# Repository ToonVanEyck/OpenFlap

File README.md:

# OpenFlap

!!! warning

    🚨 This is still a work in progress. Using the the code and files in this repository to create your own display is not recommended at the moment! 🚨

The OpenFlap project aims to create a open source, affordable split-flap display for the makers and tinkerers of the world.
This repository houses all the required files to build, program and modify your very own split-flap display. 

[**Read the Docs**](https://toonvaneyck.github.io/OpenFlap/)

## Specifications

- 48 Flaps per module.
- 49mm x 70mm Character size.
- Stackable & Chainable.
- Daisy chain communication.
- Per module configuration & calibration.
- HTTP API available.
- Modular design.
- 3D printable parts.

## Design Philosophy

The OpenFlap system is designed to be modular and expandable, using common components and manufacturing techniques such as 3D printing and printed circuit boards.

The OpenFlap system uses DC geared motors instead of traditional stepper motors. This simplifies the mechanical design and reduces the cost of the system. Additionally this reduces the power consumption of the system and allows the split-flap display to rotate faster than the traditionally used stepper motors. 

The OpenFlap system is designed to be as plug and play as possible. The system is able to determine it's own display size, and should only require calibration once.

The OpenFlap system has a web interface that allows local control of the display. The web interface uses a HTTP API to communicate with the display, this API also allows external services to communicate with the display. No authentication or security measures are implemented at the moment.

The OpenFlap system can connect to your local WiFi network or host it's own network.

## I want to ...

[... know more about how the OpenFlap system works.](docs/architecture.md)

[... build my own OpenFlap display.](todo)

[... contribute to the OpenFlap project.](docs/developing.md)

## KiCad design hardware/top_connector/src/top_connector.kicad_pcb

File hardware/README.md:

Hardware
========

All PCB's are designed in Fusion 360, the source files can be accessed an copied through the links below:

Module
------
### Side Panel
- [side panel: Electronic Design](https://a360.co/3LnqHKp)
- [side panel: PCB](https://a360.co/3OHfgiH)
- [side panel: Schematic](https://a360.co/3EQSoZI)
- [side panel: 3D](https://a360.co/3vO3oD5)

### Flap
- [flap profile: PCB](https://a360.co/3KnExLN)
- [flap profile: 3D](https://a360.co/3KmTDAU)

### Encoder Wheel
- [wheel: PCB](https://a360.co/3LnqMxH)
- [wheel: 3D](https://a360.co/37JMbTs)

Top-Con
-------
- [top-con: Electronic Design](https://a360.co/3KmcPPo)
- [top-con: PCB](https://a360.co/36RFDl1)
- [top-con: Schematic](https://a360.co/3Mybp5H)
- [top-con: 3D](https://a360.co/3ETtb0O)

Controller
----------
- [controller: Electronic Design](https://a360.co/3vmdjzr)
- [controller: PCB](https://a360.co/3LnqmHD)
- [controller: Schematic](https://a360.co/3xTXOSp)
- [controller: 3D](https://a360.co/3rY5W0q)

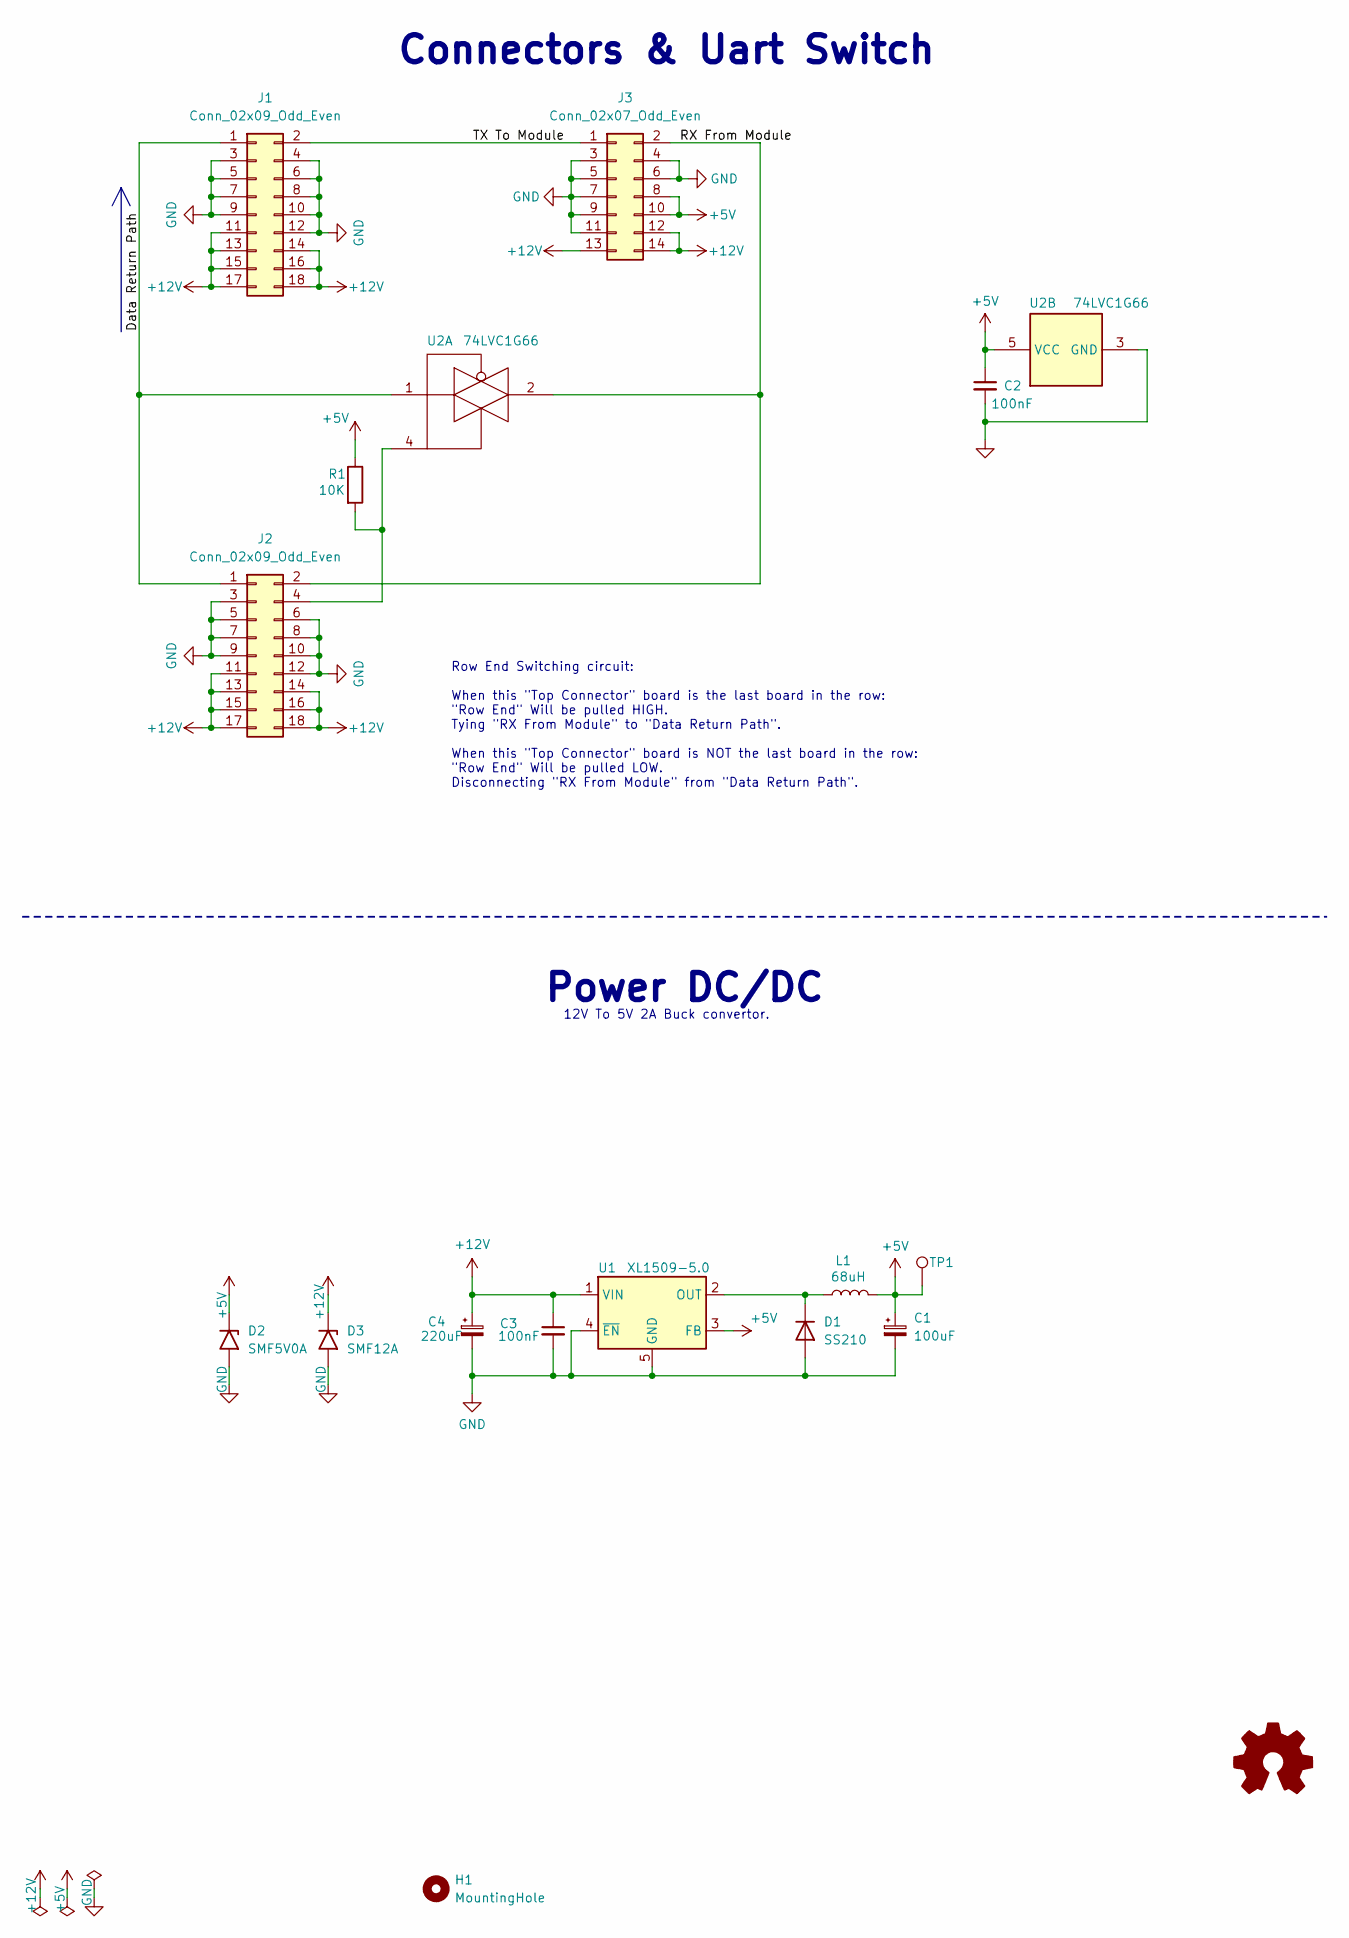
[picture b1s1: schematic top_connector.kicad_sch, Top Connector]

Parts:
C1: 100uF; CP_EIA-3528-21_Kemet-B; LCSC C16133
C2, C3: 100nF; C_0805_2012Metric
C4: 220uF; CP_Elec_6.3x7.7; LCSC C280399
D1: SS210; D_SMA; LCSC C14996
D2: SMF5V0A; D_SMF
D3: SMF12A; D_SMF
H1: MountingHole; MountingHole_2.7mm_M2.5
J1, J2: Conn_02x09_Odd_Even; IDC-Header_2x09_P2.54mm_Vertical
J3: Conn_02x07_Odd_Even; Samtec_HLE-107-02-xxx-DV-BE-A_2x07_P2.54mm_Horizontal
L1: 68uH; L_Sunlord_SWPA6045S; LCSC C53663
R1: 10K; R_0805_2012Metric
TP1: TestPoint; TestPoint_Pad_D1.5mm
U1: XL1509-5.0; SOIC-8_3.9x4.9mm_P1.27mm; LCSC C61063
U2: 74LVC1G66; SOT-23-5; LCSC C5375974

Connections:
+5V: C1.1, C2.1, D2.1 (A1), J3.8, J3.10, L1.2, R1.1, TP1.1, U1.3 (FB), U2.5 (VCC)
+12V: C3.1, C4.1, D3.1 (A1), J1.11, J1.13, J1.14, J1.15, J1.16, J1.17, J1.18, J2.11, J2.13, J2.14, J2.15, J2.16, J2.17, J2.18, J3.12, J3.13, J3.14, U1.1 (VIN)
/Data Return Path: J1.1, J2.1, U2.1
/RX From Module: J2.2, J3.2, U2.2
/TX To Module: J1.2, J3.1
GND: C1.2, C2.2, C3.2, C4.2, D1.2 (A), D2.2 (A2), D3.2 (A2), J1.3, J1.4, J1.5, J1.6, J1.7, J1.8, J1.9, J1.10, J1.12, J2.3, J2.5, J2.6, J2.7, J2.8, J2.9, J2.10, J2.12, J3.3, J3.4, J3.5, J3.6, J3.7, J3.9, J3.11, U1.4 (~EN), U1.5 (GND), U1.6 (GND), U1.7 (GND), U1.8 (GND), U2.3 (GND)
unnamed: D1.1 (K), L1.1, U1.2 (OUT)
unnamed: J2.4, R1.2, U2.4

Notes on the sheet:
Power DC/DC
12V To 5V 2A Buck convertor.
Row End Switching circuit: When this "Top Connector" board is the last board in the row: "Row End" Will be pulled HIGH. Tying "RX From Module" to "Data Return Path". When this "Top Connector" board is NOT the last board in the row: "Row End" Will be pulled LOW. Disconnecting "RX From Module" from "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
Connectors & Uart Switch

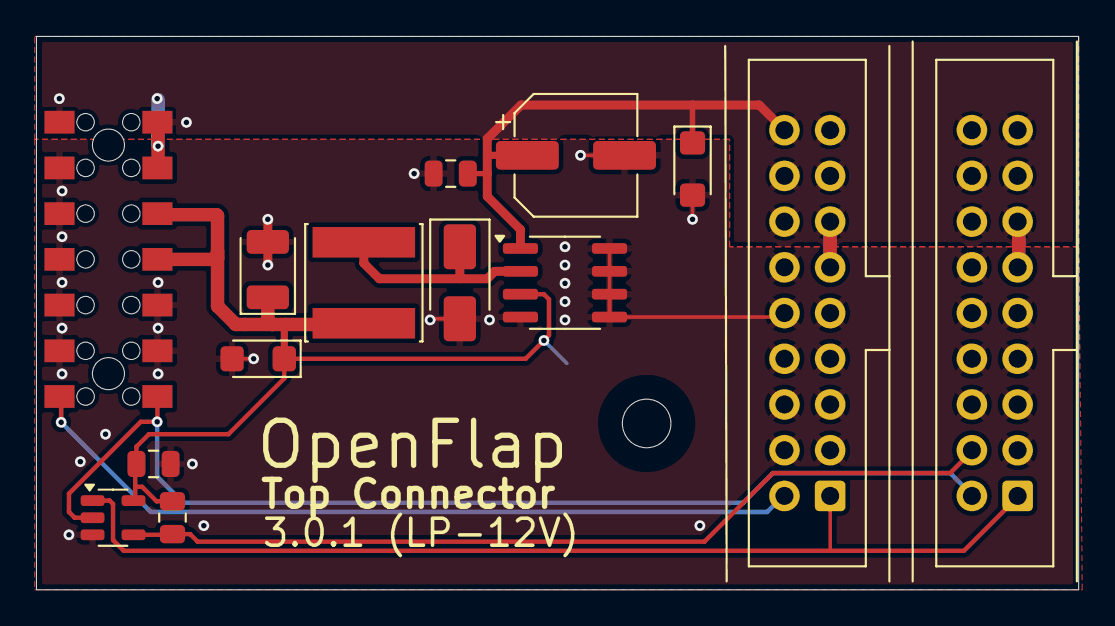
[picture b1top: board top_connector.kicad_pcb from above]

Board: 2 copper layers, 57.9 x 30.7 mm, 16 parts (1 on the bottom side), 8 nets.

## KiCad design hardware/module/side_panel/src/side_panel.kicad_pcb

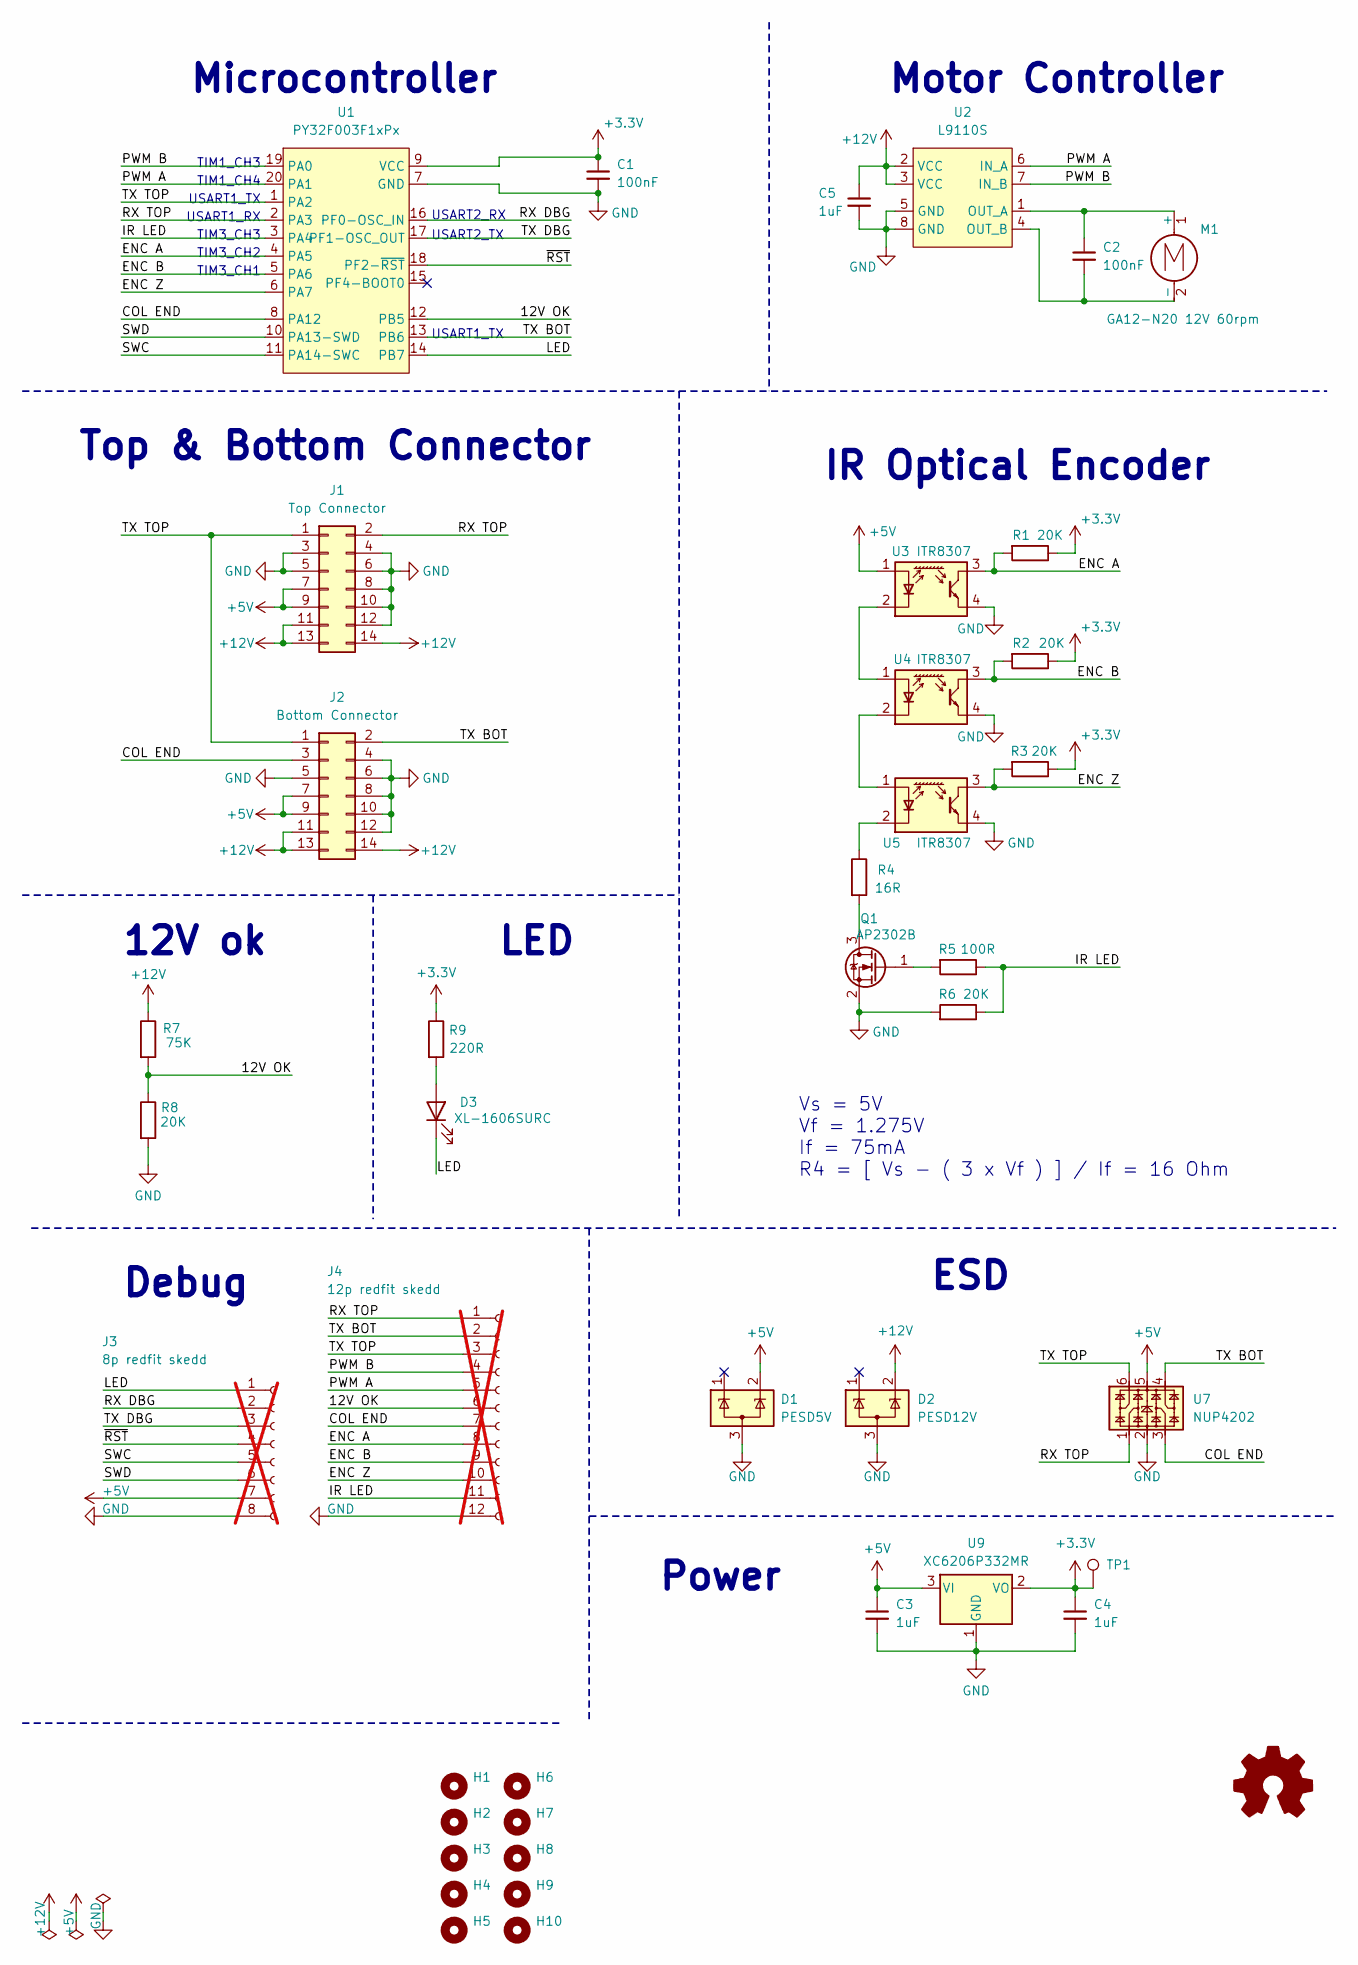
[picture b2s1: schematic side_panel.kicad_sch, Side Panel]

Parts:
C1, C2: 100nF; C_0805_2012Metric
C3, C4, C5: 1uF; C_0805_2012Metric
D1: PESD5V; SOT-23-3
D2: PESD12V; SOT-23-3
D3: XL-1606SURC; LED_Kingbright_APA1606_1.6x0.6mm_Horizontal; LCSC C965860
H1, H2, H3, H4, H5, H6, H7, H8, H9, H10: MountingHole; MountingHole_2.7mm
J1: Top Connector; PinHeader_2x07_P2.54mm_Horizontal
J2: Bottom Connector; PinSocket_2x07_P2.54mm_Horizontal
J3: 8p redfit skedd; 490107670812; not fitted
J4: 12p redfit skedd; 490107671212; not fitted
M1: GA12-N20 12V 60rpm; GA12-N20 Motor Vertical
Q1: AP2302B; SOT-23; LCSC C406812
R1, R2, R3, R6, R8: 20K; R_0805_2012Metric
R4: 16R; R_0805_2012Metric
R5: 100R; R_0805_2012Metric
R7: 75K; R_0805_2012Metric
R9: 220R; R_0805_2012Metric
TP1: TestPoint; TestPoint_Pad_D1.5mm
U1: PY32F003F1xPx; TSSOP-20_4.4x6.5mm_P0.65mm; LCSC C5379864
U2: L9110S; SOP-8_3.76x4.96mm_P1.27mm; LCSC C2984833
U3, U4, U5: ITR8307; OnSemi_CASE100CY; LCSC C81632
U7: NUP4202; SOT-23-6; LCSC C5199189
U9: XC6206P332MR; SOT-23-3

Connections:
+3.3V: C1.1, C4.1, R1.1, R2.1, R3.1, R9.1, TP1.1, U1.9 (VCC), U9.2 (VO)
+5V: C3.1, D1.2 (K), J1.7, J1.9, J2.7, J2.9, J3.7, U3.1 (A), U7.5, U9.3 (VI)
+12V: C5.1, D2.2 (K), J1.11, J1.13, J1.14, J2.11, J2.13, J2.14, R7.1, U2.2 (VCC), U2.3 (VCC)
/12V OK: J4.6, R7.2, R8.1, U1.12 (PB5)
/COL END: J2.3, J4.7, U1.8 (PA12), U7.3
/ENC A: J4.8, R1.2, U1.4 (PA5), U3.3
/ENC B: J4.9, R2.2, U1.5 (PA6), U4.3
/ENC Z: J4.10, R3.2, U1.6 (PA7), U5.3
/IR LED: J4.11, R5.1, R6.1, U1.3 (PA4)
/LED: D3.1 (K), J3.1, U1.14 (PB7)
/PWM A: J4.5, U1.20 (PA1), U2.6 (IN_A)
/PWM B: J4.4, U1.19 (PA0), U2.7 (IN_B)
/RX DBG: J3.2, U1.16 (PF0-OSC_IN)
/RX TOP: J1.2, J4.1, U1.2 (PA3), U7.1
/SWC: J3.5, U1.11 (PA14-SWC)
/SWD: J3.6, U1.10 (PA13-SWD)
/TX BOT: J2.2, J4.2, U1.13 (PB6), U7.4
/TX DBG: J3.3, U1.17 (PF1-OSC_OUT)
/TX TOP: J1.1, J2.1, J4.3, U1.1 (PA2), U7.6
/~RST: J3.4, U1.18 (PF2-~RST)
GND: C1.2, C3.2, C4.2, C5.2, D1.3 (A), D2.3 (A), J1.3, J1.4, J1.5, J1.6, J1.8, J1.10, J1.12, J2.4, J2.5, J2.6, J2.8, J2.10, J2.12, J3.8, J4.12, Q1.2 (S), R6.2, R8.2, U1.7 (GND), U2.5 (GND), U2.8 (GND), U3.4, U4.4, U5.4, U7.2, U9.1 (GND)
unnamed: D3.2 (A), R9.2
unnamed: C2.1, M1.1 (+), U2.1 (OUT_A)
unnamed: C2.2, M1.2 (-), U2.4 (OUT_B)
unnamed: Q1.3 (D), R4.2
unnamed: Q1.1 (G), R5.2
unnamed: U3.2 (K), U4.1 (A)
unnamed: U4.2 (K), U5.1 (A)
unnamed: R4.1, U5.2 (K)

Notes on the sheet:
USART1_RX
USART1_TX
LED
TIM1_CH3
Top & Bottom Connector
TIM3_CH2
Power
IR Optical Encoder
12V ok
TIM1_CH4
USART2_RX
TIM3_CH3
Vs = 5V Vf = 1.275V If = 75mA R4 = [ Vs - ( 3 x Vf ) ] / If = 16 Ohm
ESD
Motor Controller
Microcontroller
USART2_TX
TIM3_CH1
Debug

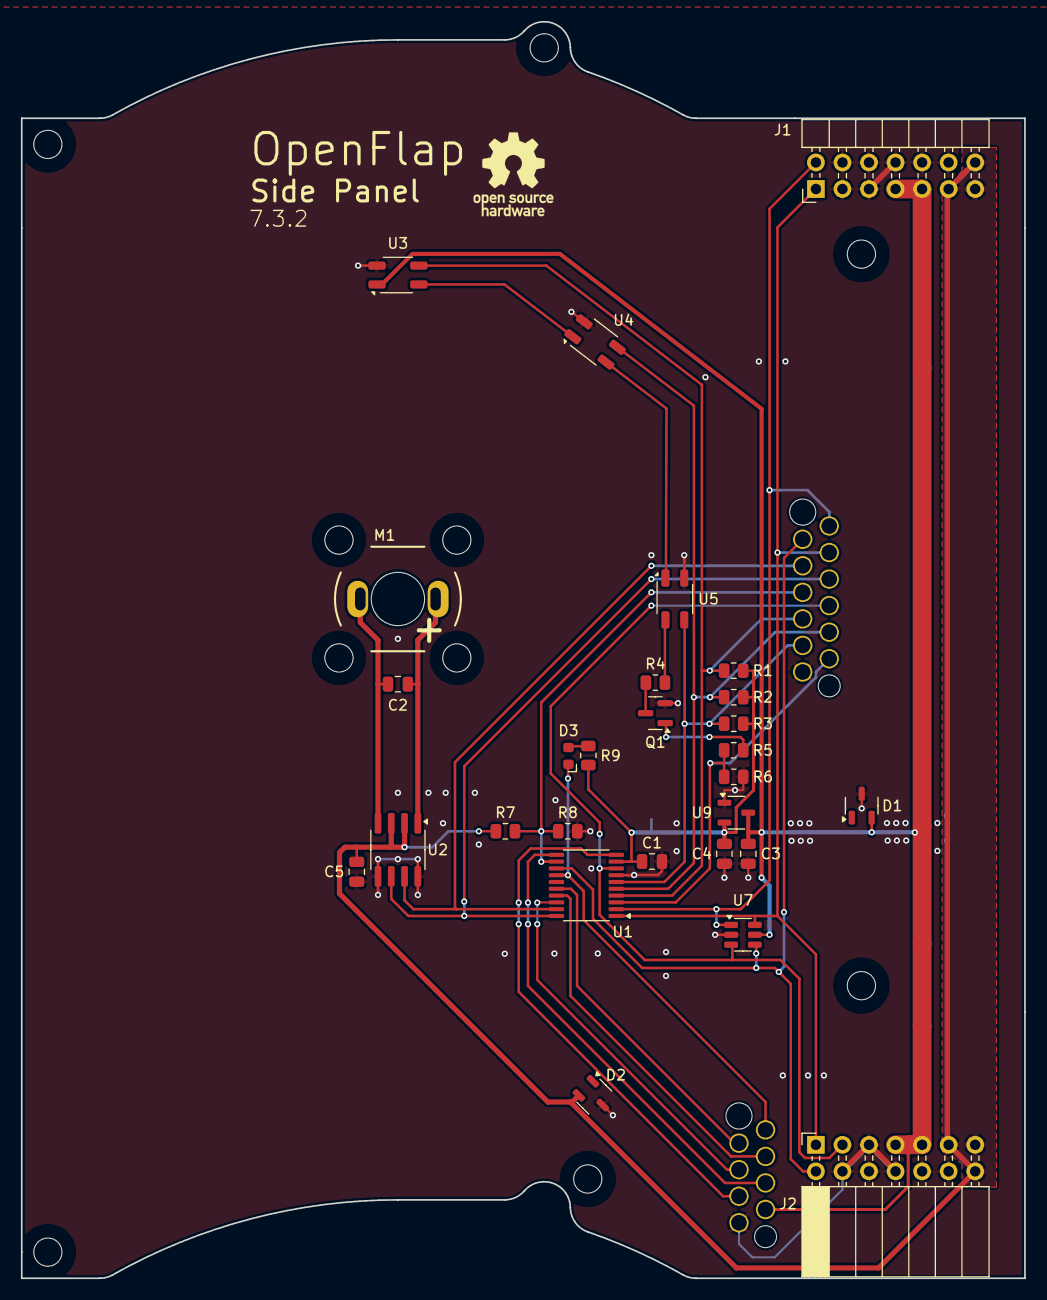
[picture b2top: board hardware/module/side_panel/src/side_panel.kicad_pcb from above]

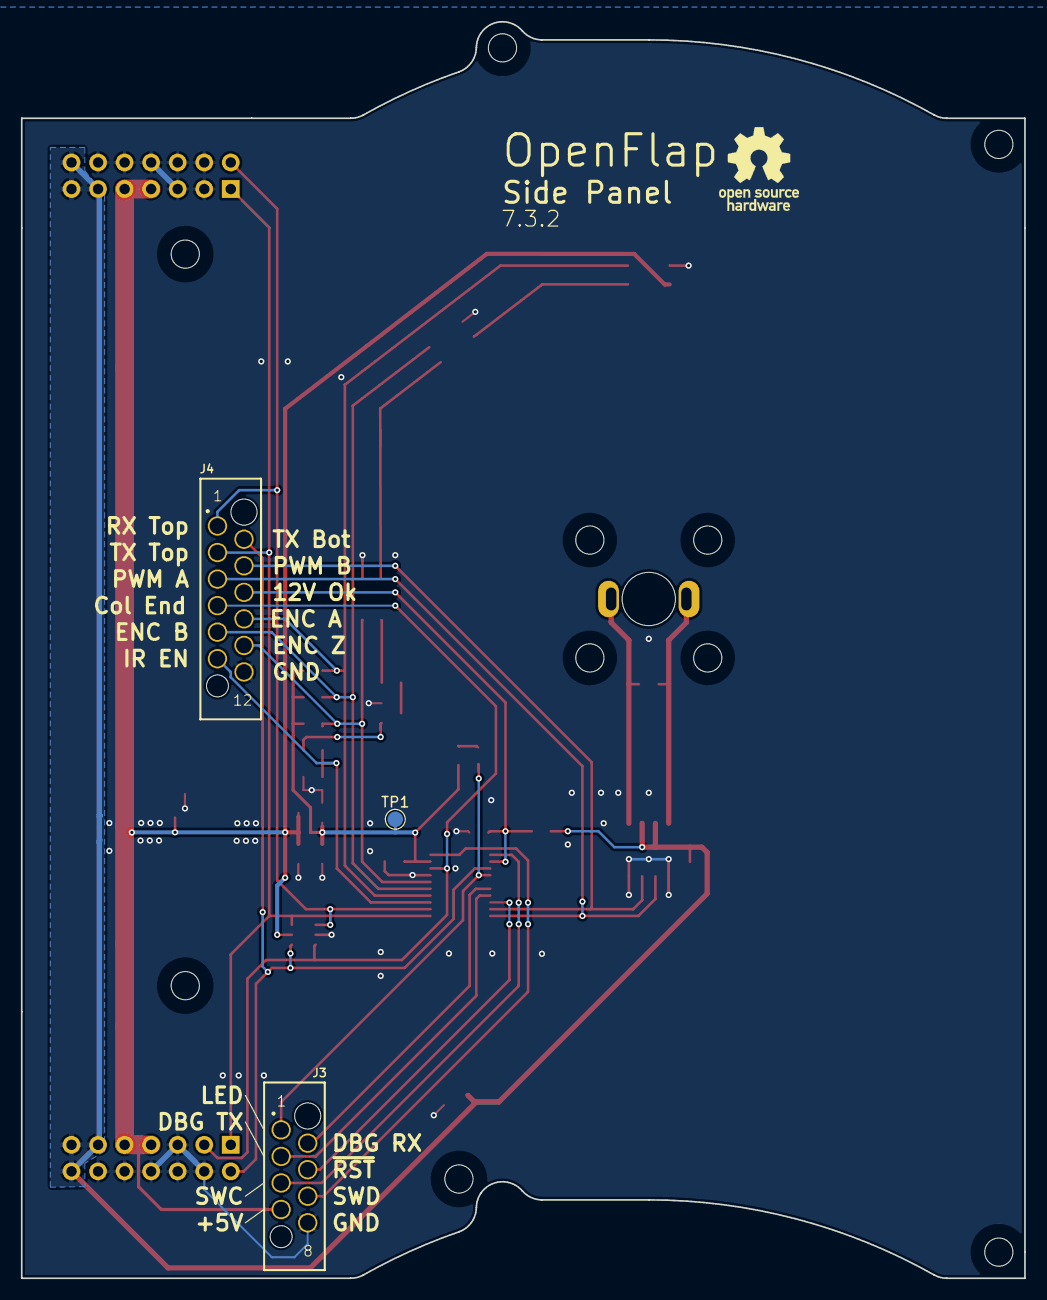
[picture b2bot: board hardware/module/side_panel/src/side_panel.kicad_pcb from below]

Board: 2 copper layers, 96.0 x 120.2 mm, 43 parts (4 on the bottom side), 29 nets.

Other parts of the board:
OSHW-LOGO-1, OSHW-LOGO-2: OSHW-Logo_7.5x8mm_SilkScreen

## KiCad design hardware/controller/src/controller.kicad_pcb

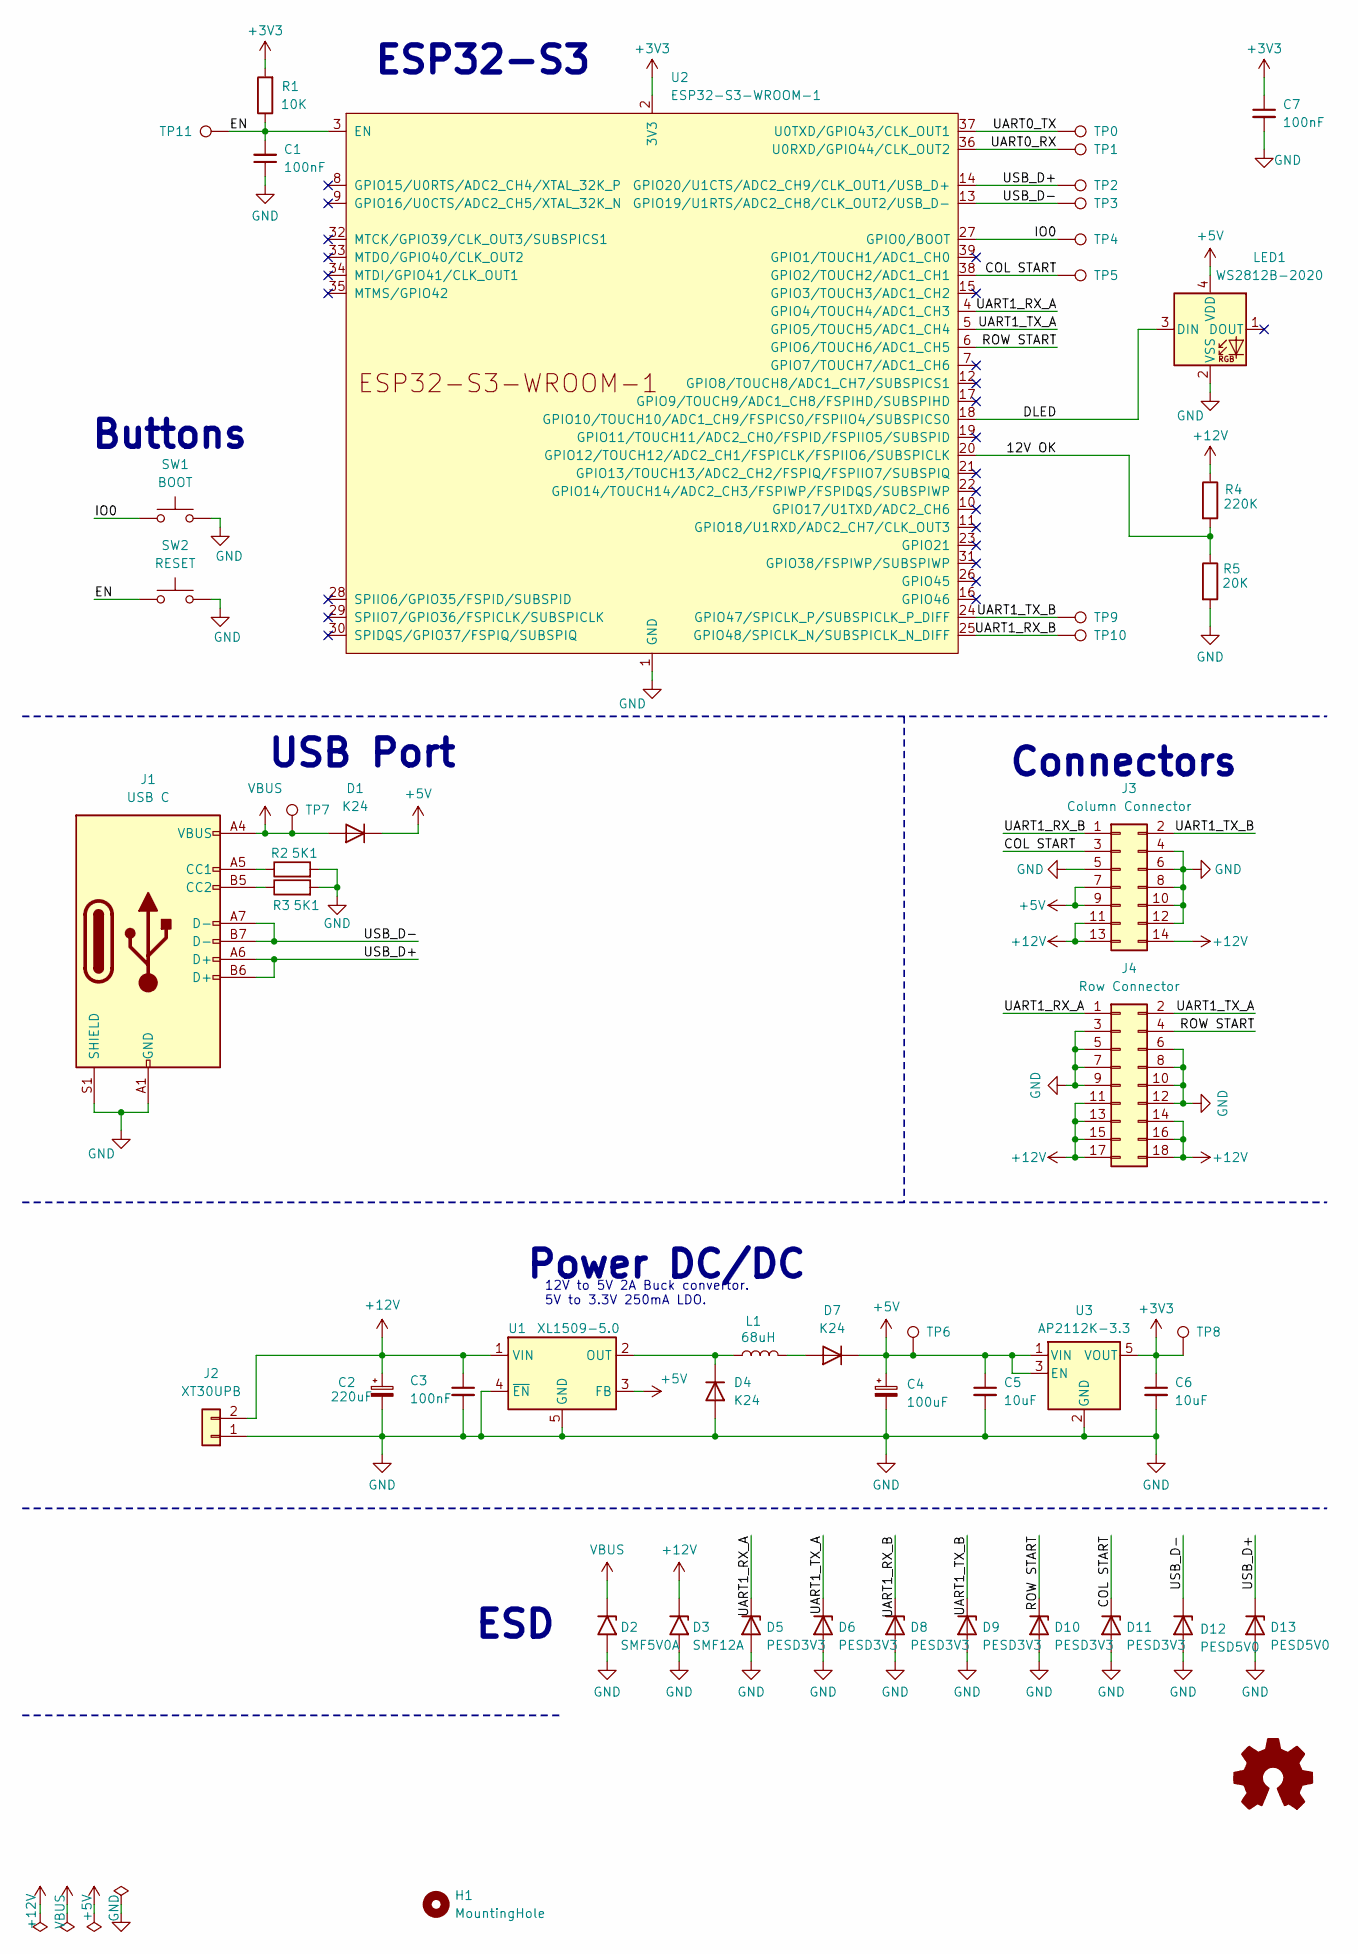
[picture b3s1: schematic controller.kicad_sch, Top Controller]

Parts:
C1, C3, C7: 100nF; C_0805_2012Metric
C2: 220uF; CP_Elec_6.3x7.7; LCSC C280399
C4: 100uF; CP_EIA-3528-21_Kemet-B; LCSC C16133
C5, C6: 10uF; C_0805_2012Metric
D1, D4, D7: K24; D_SMF; LCSC C5199107
D2: SMF5V0A; D_SMF
D3: SMF12A; D_SMF
D5, D6, D8, D9, D10, D11: PESD3V3; D_SOD-523; LCSC C5180303
D12, D13: PESD5V0; D_SOD-523; LCSC C19725076
H1: MountingHole; MountingHole_2.7mm_M2.5
J1: USB C; MC-803LS-HXXX; LCSC C3039302
J2: XT30UPB; AMASS_XT30UPB-M_1x02_P5.0mm_Vertical; LCSC C428721
J3: Column Connector; Samtec_HLE-107-02-xxx-DV-BE-A_2x07_P2.54mm_Horizontal
J4: Row Connector; IDC-Header_2x09_P2.54mm_Vertical
L1: 68uH; L_Sunlord_SWPA6045S; LCSC C53663
LED1: WS2812B-2020; LED_WS2812B-2020_PLCC4_2.0x2.0mm; LCSC C41413181
R1: 10K; R_0603_1608Metric
R2, R3: 5K1; R_0603_1608Metric
R4: 220K; R_0603_1608Metric
R5: 20K; R_0603_1608Metric
SW1: BOOT; SW_SPST_EVQP7C; LCSC C528965
SW2: RESET; SW_SPST_EVQP7C; LCSC C528965
TP0, TP1, TP2, TP3, TP4, TP5, TP6, TP7, TP8, TP9, TP10, TP11: TestPoint; TestPoint_Pad_D1.5mm
U1: XL1509-5.0; SOIC-8_3.9x4.9mm_P1.27mm; LCSC C61063
U2: ESP32-S3-WROOM-1
U3: AP2112K-3.3; SOT-23-5

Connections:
+3V3: C6.1, C7.1, R1.2, TP8.1, U2.2 (3V3), U3.5 (VOUT)
+5V: C4.1, C5.1, D1.1 (K), D7.1 (K), J3.7, J3.9, LED1.4 (VDD), TP6.1, U1.3 (FB), U3.1 (VIN), U3.3 (EN)
+12V: C2.1, C3.1, D3.1 (A1), J2.2, J3.11, J3.13, J3.14, J4.11, J4.13, J4.14, J4.15, J4.16, J4.17, J4.18, R4.1, U1.1 (VIN)
/12V OK: R4.2, R5.1, U2.20 (GPIO12/TOUCH12/ADC2_CH1/FSPICLK/FSPIIO6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)
/COL START: D11.1 (K), J3.3, TP5.1, U2.38 (GPIO2/TOUCH2/ADC1_CH1)
/DLED: LED1.3 (DIN), U2.18 (GPIO10/TOUCH10/ADC1_CH9/FSPICS0/FSPIIO4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)
/EN: C1.2, R1.1, SW2.1, TP11.1, U2.3 (EN)
/IO0: SW1.1, TP4.1, U2.27 (GPIO0/BOOT)
/ROW START: D10.1 (K), J4.4, U2.6 (GPIO6/TOUCH6/ADC1_CH5)
/UART0_RX: TP1.1, U2.36 (U0RXD/GPIO44/CLK_OUT2)
/UART0_TX: TP0.1, U2.37 (U0TXD/GPIO43/CLK_OUT1)
/UART1_RX_A: D5.1 (K), J4.1, U2.4 (GPIO4/TOUCH4/ADC1_CH3)
/UART1_RX_B: D8.1 (K), J3.1, TP10.1, U2.25 (GPIO48/SPICLK_N/SUBSPICLK_N_DIFF)
/UART1_TX_A: D6.1 (K), J4.2, U2.5 (GPIO5/TOUCH5/ADC1_CH4)
/UART1_TX_B: D9.1 (K), J3.2, TP9.1, U2.24 (GPIO47/SPICLK_P/SUBSPICLK_P_DIFF)
/USB_D+: D13.1 (K), J1.A6 (D+), J1.B6 (D+), TP2.1, U2.14 (GPIO20/U1CTS/ADC2_CH9/CLK_OUT1/USB_D+)
/USB_D-: D12.1 (K), J1.A7 (D-), J1.B7 (D-), TP3.1, U2.13 (GPIO19/U1RTS/ADC2_CH8/CLK_OUT2/USB_D-)
GND: C1.1, C2.2, C3.2, C4.2, C5.2, C6.2, C7.2, D2.2 (A2), D3.2 (A2), D4.2 (A), D5.2 (A), D6.2 (A), D8.2 (A), D9.2 (A), D10.2 (A), D11.2 (A), D12.2 (A), D13.2 (A), J1.A1 (GND), J1.A12 (GND), J1.B1 (GND), J1.B12 (GND), J1.S1 (SHIELD), J2.1, J3.4, J3.5, J3.6, J3.8, J3.10, J3.12, J4.3, J4.5, J4.6, J4.7, J4.8, J4.9, J4.10, J4.12, LED1.2 (VSS), R2.2, R3.2, R5.2, SW1.2, SW2.2, U1.4 (~EN), U1.5 (GND), U1.6 (GND), U1.7 (GND), U1.8 (GND), U2.1 (GND), U2.40 (GND), U2.41 (GND), U3.2 (GND)
unnamed: D4.1 (K), L1.1, U1.2 (OUT)
unnamed: D7.2 (A), L1.2
unnamed: J1.A5 (CC1), R2.1
unnamed: J1.B5 (CC2), R3.1
VBUS: D1.2 (A), D2.1 (A1), J1.A4 (VBUS), J1.A9 (VBUS), J1.B4 (VBUS), J1.B9 (VBUS), TP7.1

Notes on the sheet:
Power DC/DC
ESD
Buttons
USB Port
12V to 5V 2A Buck convertor. 5V to 3.3V 250mA LDO.
Connectors
ESP32-S3

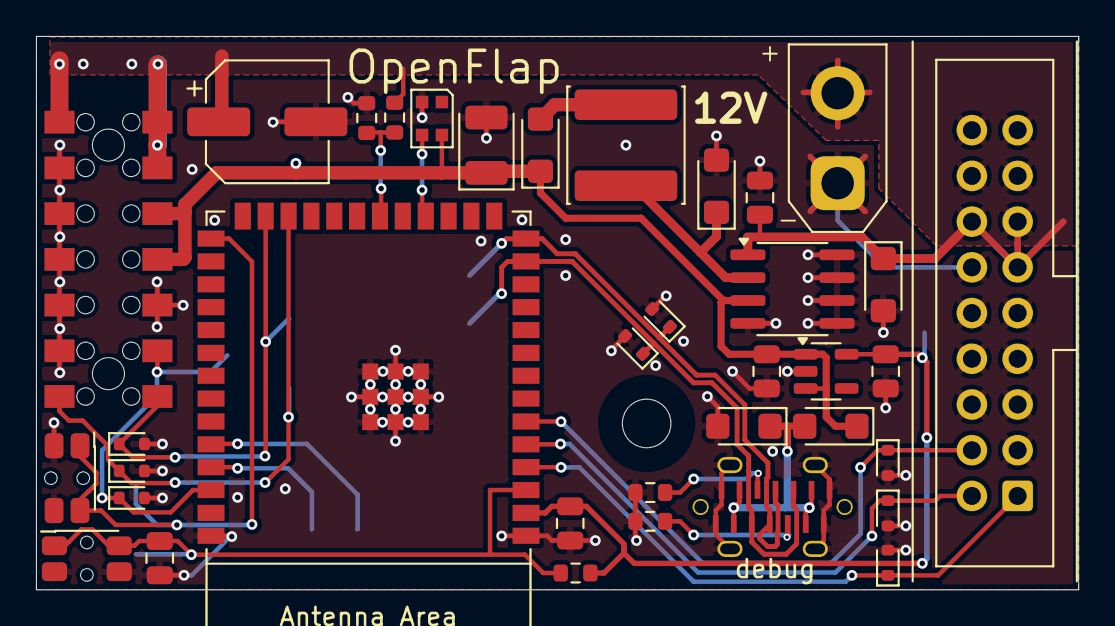
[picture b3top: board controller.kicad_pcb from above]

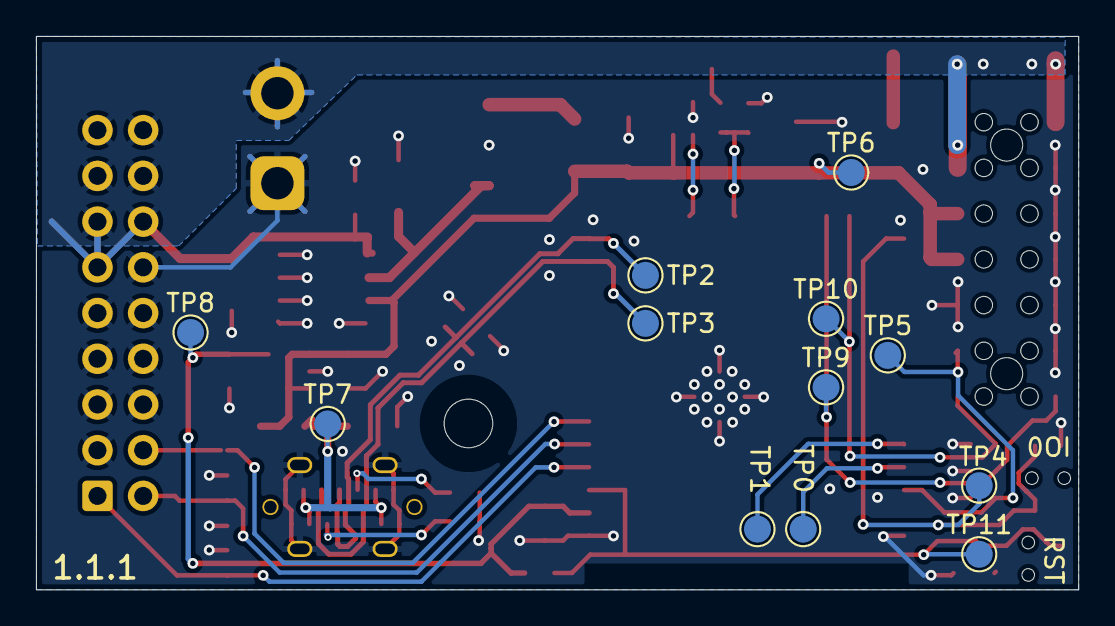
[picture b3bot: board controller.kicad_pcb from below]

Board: 2 copper layers, 57.9 x 30.7 mm, 49 parts (12 on the bottom side), 23 nets.

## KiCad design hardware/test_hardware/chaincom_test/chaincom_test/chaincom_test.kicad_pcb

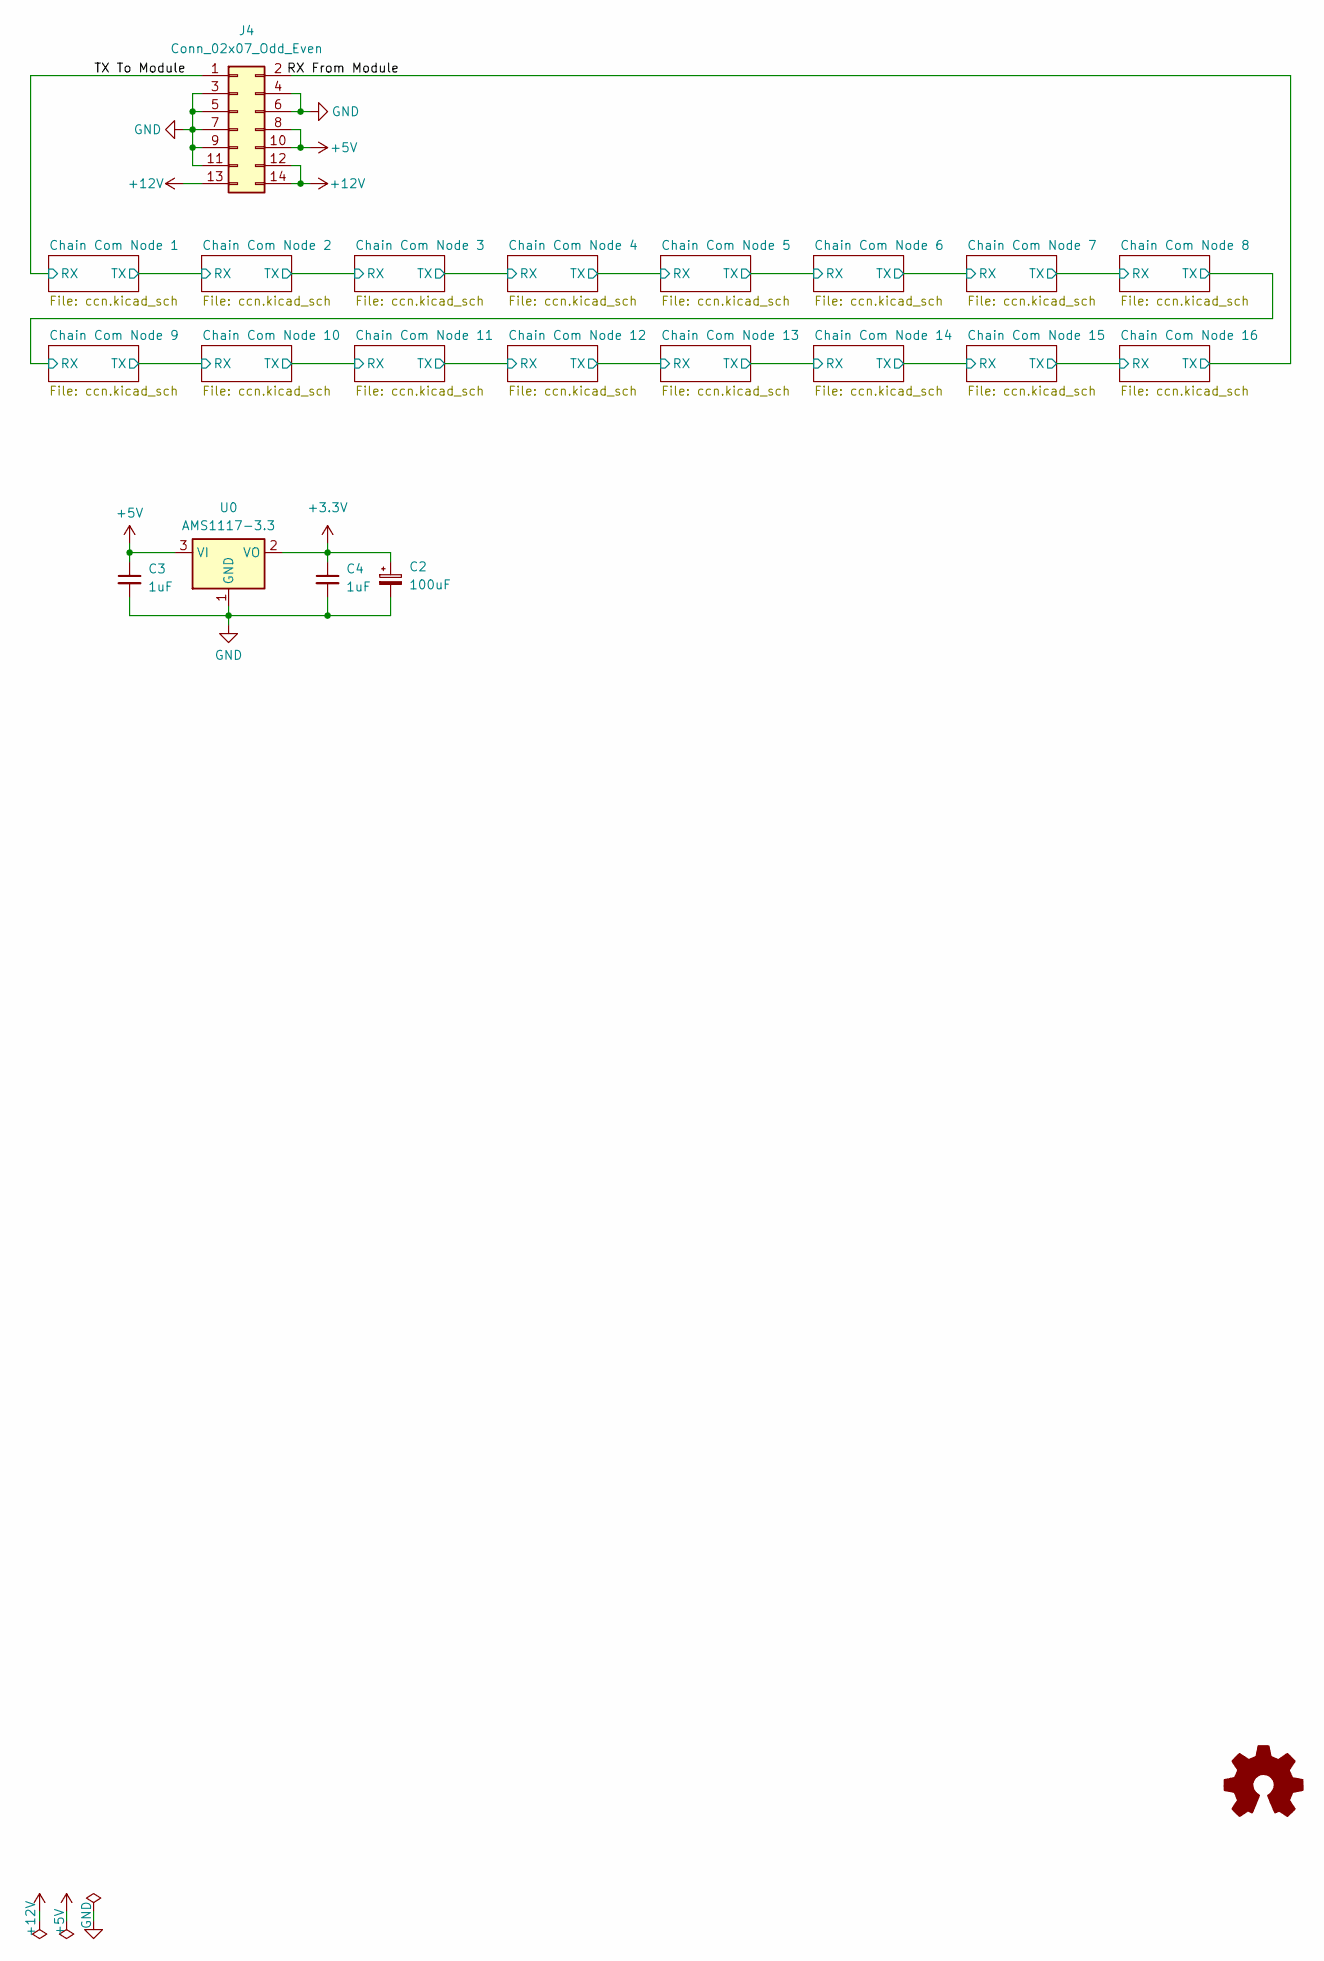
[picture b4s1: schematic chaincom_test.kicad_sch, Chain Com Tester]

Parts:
C2: 100uF; CP_EIA-3528-21_Kemet-B; LCSC C16133
C3, C4: 1uF; C_0805_2012Metric
J4: Conn_02x07_Odd_Even; PinHeader_2x07_P2.54mm_Vertical
U0: AMS1117-3.3; SOT-223-3_TabPin2; LCSC C18164485

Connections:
+3.3V: C2.1, C4.1, U0.2 (VO); also elsewhere on the board
+5V: C3.1, J4.8, J4.10, U0.3 (VI)
+12V: J4.12, J4.13, J4.14
/RX From Module: J4.2; also elsewhere on the board
/TX To Module: J4.1; also elsewhere on the board
GND: C2.2, C3.2, C4.2, J4.3, J4.4, J4.5, J4.6, J4.7, J4.9, J4.11, U0.1 (GND); also elsewhere on the board
